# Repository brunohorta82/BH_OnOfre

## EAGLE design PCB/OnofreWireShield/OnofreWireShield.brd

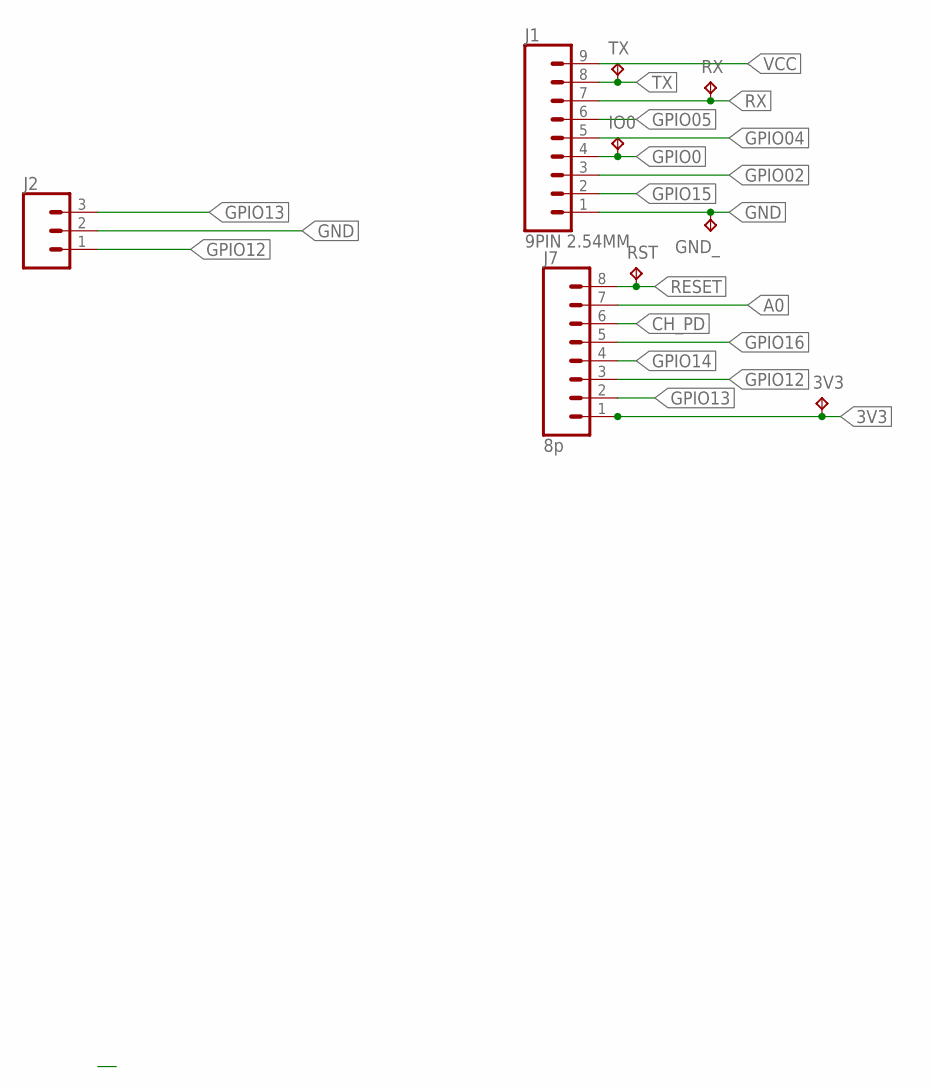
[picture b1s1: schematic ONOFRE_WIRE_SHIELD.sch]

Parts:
3V3: TPB1,27; B1,27
GND_: TPB1,27; B1,27
IO0: TPB1,27; B1,27
J1: 9PIN 2.54MM; 1X09
J2: CONN_03; 1X03
J7: 8p; 1X08
RST: TPB1,27; B1,27
RX: TPB1,27; B1,27
TX: TPB1,27; B1,27

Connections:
3V3: 3V3.TP, J7.1
A0: J7.7
CH_PD: J7.6
GND: GND_.TP, J1.1, J2.2
GPIO0: IO0.TP, J1.4
GPIO02: J1.3
GPIO04: J1.5
GPIO05: J1.6
GPIO12: J2.1, J7.3
GPIO13: J2.3, J7.2
GPIO14: J7.4
GPIO15: J1.2
GPIO16: J7.5
RESET: J7.8, RST.TP
RX: J1.7, RX.TP
TX: J1.8, TX.TP
VCC: J1.9

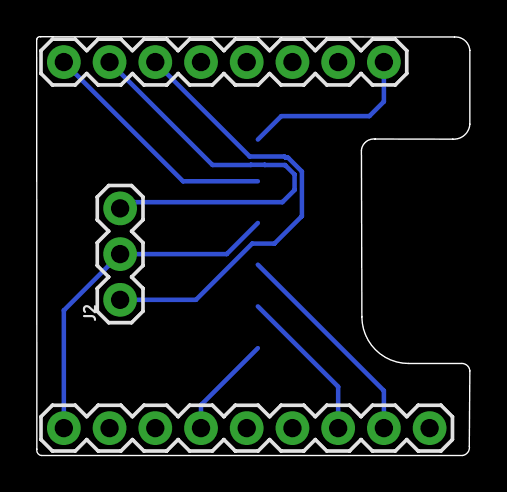
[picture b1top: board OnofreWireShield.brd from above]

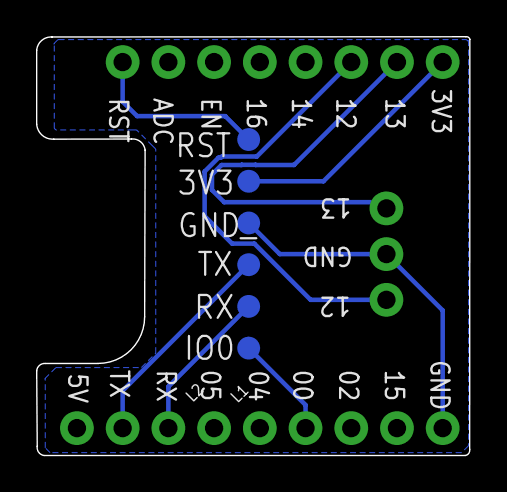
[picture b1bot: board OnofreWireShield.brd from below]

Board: 2 copper layers, 24.1 x 23.3 mm, 9 parts (6 on the bottom side), 8 nets.

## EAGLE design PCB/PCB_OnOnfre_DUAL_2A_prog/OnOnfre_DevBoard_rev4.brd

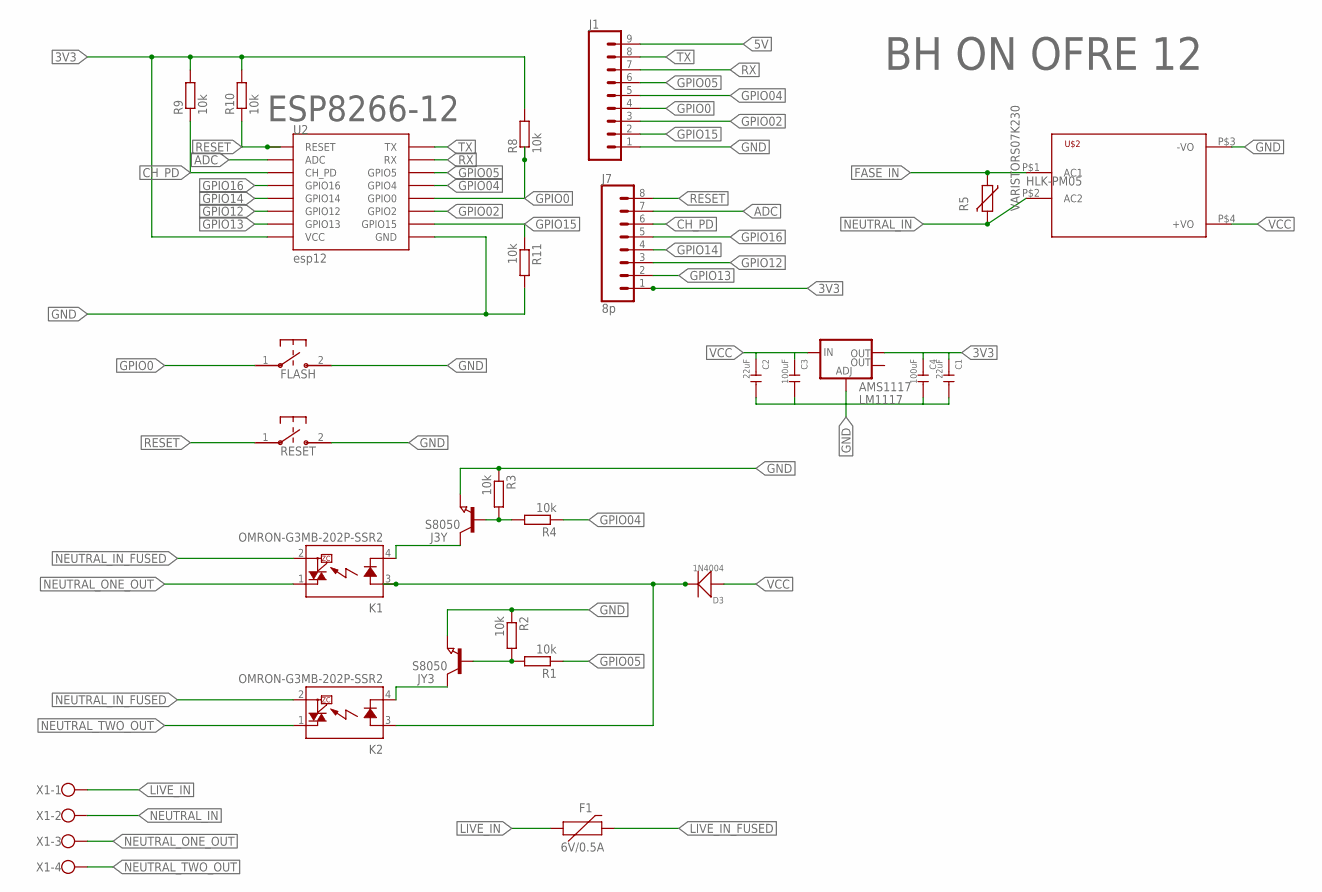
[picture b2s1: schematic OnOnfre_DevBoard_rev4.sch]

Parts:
AMS1117: LM1117; SOT223
C1, C2: 22uF; C1206
C3, C4: 100uF; C1206
D3: 1N4004; DO-214AC
F1: 6V/0.5A; 1206
FLASH: B3U-1000P-2P-SMD; B3U-1000P
J1: CONN_09; 1X09
J3Y: S8050; SOT23
J7: 8p; 1X08
JY3: S8050; SOT23
K1, K2: OMRON-G3MB-202P-SSR2; OMRON-G3MB-202P-SSR
R1, R2, R3, R4, R8, R9, R10, R11: 10k; R0603
R5: VARISTORS07K230; S07K230
RESET: B3U-1000P-2P-SMD; B3U-1000P
U2: esp12; ESP12-SMD
U$2: HKLPM01
X1: W237-4

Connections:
3V3: AMS1117.2 (OUT), C1.1, C4.1, J7.1, R8.2, R9.2, R10.2, U2.VCC
5V: D3.2 (-), J1.9, K1.3 (A), K2.3 (A)
ADC: J7.7, U2.ADC
CH_PD: J7.6, R9.1, U2.CH_PD
FASE_IN: R5.1, U$2.P$1 (AC1)
GND: AMS1117.1 (ADJ), C1.2, C2.2, C3.2, C4.2, FLASH.2, J1.1, J3Y.2 (E), JY3.2 (E), R2.1, R3.1, R11.2, RESET.2, U2.GND, U$2.P$3 (-VO)
GPIO0: FLASH.1, J1.4, R8.1, U2.GPIO0
GPIO02: J1.3, U2.GPIO2
GPIO04: J1.5, R4.1, U2.GPIO4
GPIO05: J1.6, R1.1, U2.GPIO5
GPIO12: J7.3, U2.GPIO12
GPIO13: J7.2, U2.GPIO13
GPIO14: J7.4, U2.GPIO14
GPIO15: J1.2, R11.1, U2.GPIO15
GPIO16: J7.5, U2.GPIO16
LIVE_IN: F1.1, X1.1
LIVE_IN_FUSED: F1.2
unnamed: J3Y.3 (C), K1.4 (K)
unnamed: J3Y.1 (B), R3.2, R4.2
unnamed: JY3.3 (C), K2.4 (K)
unnamed: JY3.1 (B), R1.2, R2.2
NEUTRAL_IN: R5.2, U$2.P$2 (AC2), X1.2
NEUTRAL_IN_FUSED: K1.2 (DS2), K2.2 (DS2)
NEUTRAL_ONE_OUT: K1.1 (DS1), X1.3
NEUTRAL_TWO_OUT: K2.1 (DS1), X1.4
RESET: J7.8, R10.1, RESET.1, U2.RESET
RX: J1.7, U2.RXD0 (RX)
TX: J1.8, U2.TXD0 (TX)
VCC: AMS1117.3 (IN), C2.1, C3.1, D3.1 (+), U$2.P$4 (+VO)

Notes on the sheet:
HLK-PM05
BH ON OFRE 12
ESP8266-12

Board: 2 copper layers, 27 parts (5 on the bottom side), 28 nets, no tracks yet.

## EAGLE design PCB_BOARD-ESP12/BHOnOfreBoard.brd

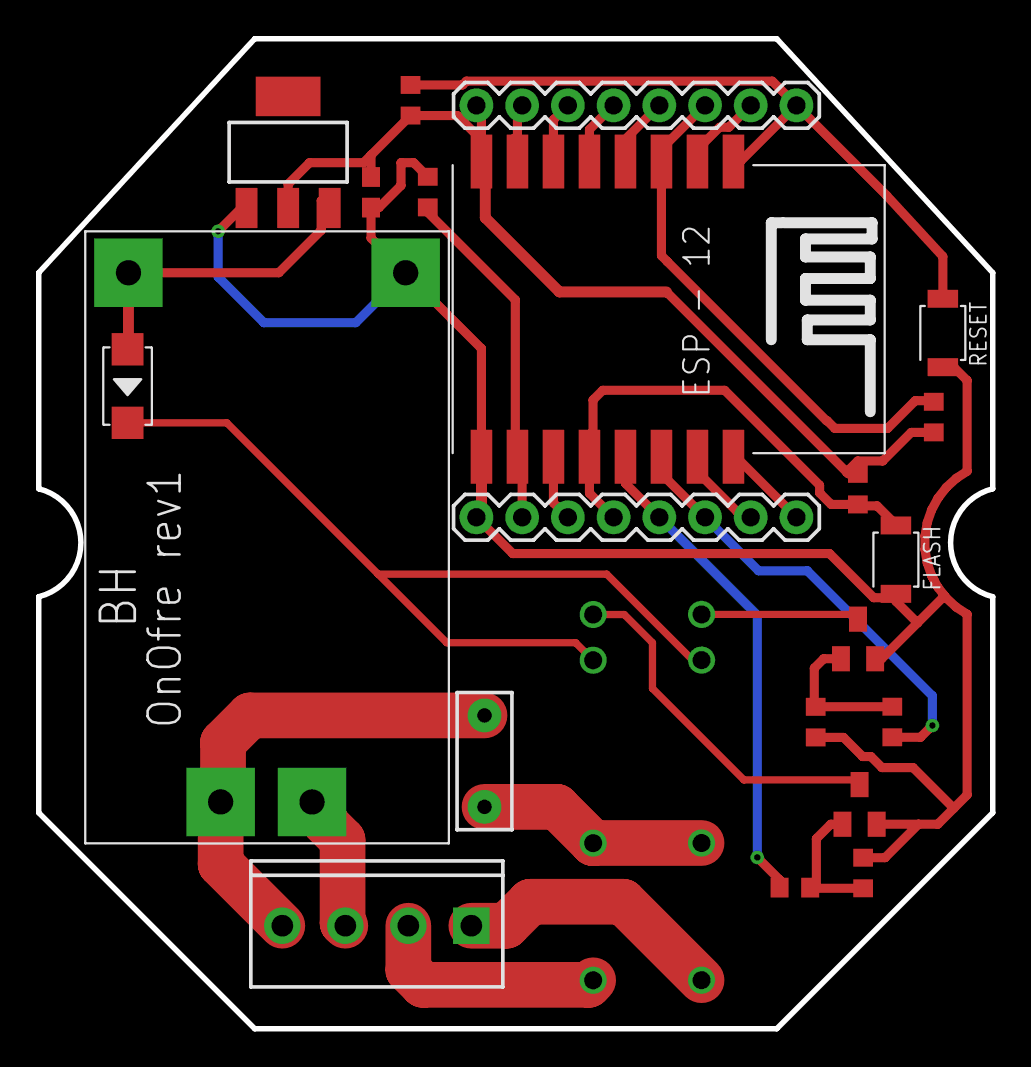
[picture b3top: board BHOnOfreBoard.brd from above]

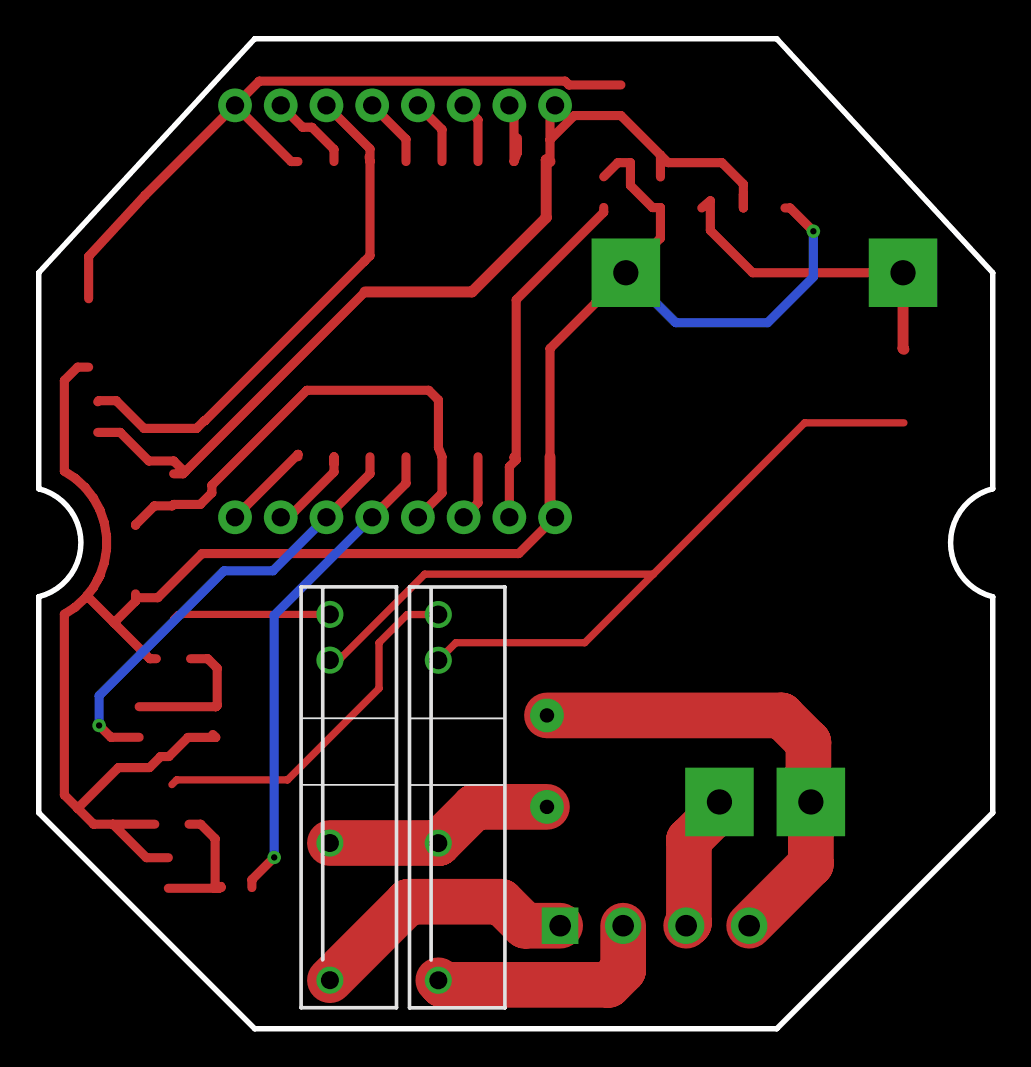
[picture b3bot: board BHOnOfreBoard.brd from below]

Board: 2 copper layers, 53.0 x 55.0 mm, 23 parts (2 on the bottom side), 27 nets.

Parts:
C4: 100nF; 0603
D3: 1N4004; DO-214AC
F1: FUSE 2A; PTH
FLASH: B3U-1000P-2P-SMD; SW2-2.6-3.0X2.5X1.2+0.4MM
J1: 4p; SCREWTERMINAL-3.5MM-4
J6, J7: 8p; 1X08
K1, K2: OMRON-G3MB-202P-SSR2; OMRON-G3MB-202P-SSR
Q1, Q2: S8050; SOT23
R1, R2, R3, R4, R8, R9, R10, R11: 10k; R0603
RESET: B3U-1000P-2P-SMD; SW2-2.6-3.0X2.5X1.2+0.4MM
U1: LM1117; SOT223
U2: esp12; ESP12-SMD
U$2: HLK-PM03

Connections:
3V3: C4.1, J7.1, R8.2, R9.2, R10.2, U1.2, U2.VCC
ADC: J7.7, U2.ADC
CH_PD: J7.6, R9.1, U2.CH_PD
FASE: J1.3, U$2.AC2
GND: C4.2, FLASH.2, J6.1, Q1.2, Q2.2, R2.1, R3.1, R11.2, RESET.2, U1.1, U2.GND, U$2.-VO
GPIO0: FLASH.1, J6.4, R8.1, U2.GPIO0
GPIO02: J6.3, U2.GPIO2
GPIO04: J6.6, R1.1, U2.GPIO4
GPIO05: J6.5, R4.1, U2.GPIO5
GPIO12: J7.3, U2.GPIO12
GPIO13: J7.2, U2.GPIO13
GPIO14: J7.4, U2.GPIO14
GPIO15: J6.2, R11.1, U2.GPIO15
GPIO16: J7.5, U2.GPIO16
unnamed: K1.4, Q1.3
unnamed: D3.2, K1.3, K2.3
unnamed: Q1.1, R3.2, R4.2
unnamed: K2.4, Q2.3
unnamed: Q2.1, R1.2, R2.2
NEUTRAL_IN: F1.P$1, J1.4, U$2.AC1
NEUTRAL_IN_FUSED: F1.P$2, K1.2, K2.2
NEUTRAL_ONE_OUT: J1.2, K1.1
NEUTRAL_TWO_OUT: J1.1, K2.1
RESET: J7.8, R10.1, RESET.1, U2.RESET
RX: J6.7, U2.RXD0
TX: J6.8, U2.TXD0
VCC: D3.1, U1.3, U$2.+VO

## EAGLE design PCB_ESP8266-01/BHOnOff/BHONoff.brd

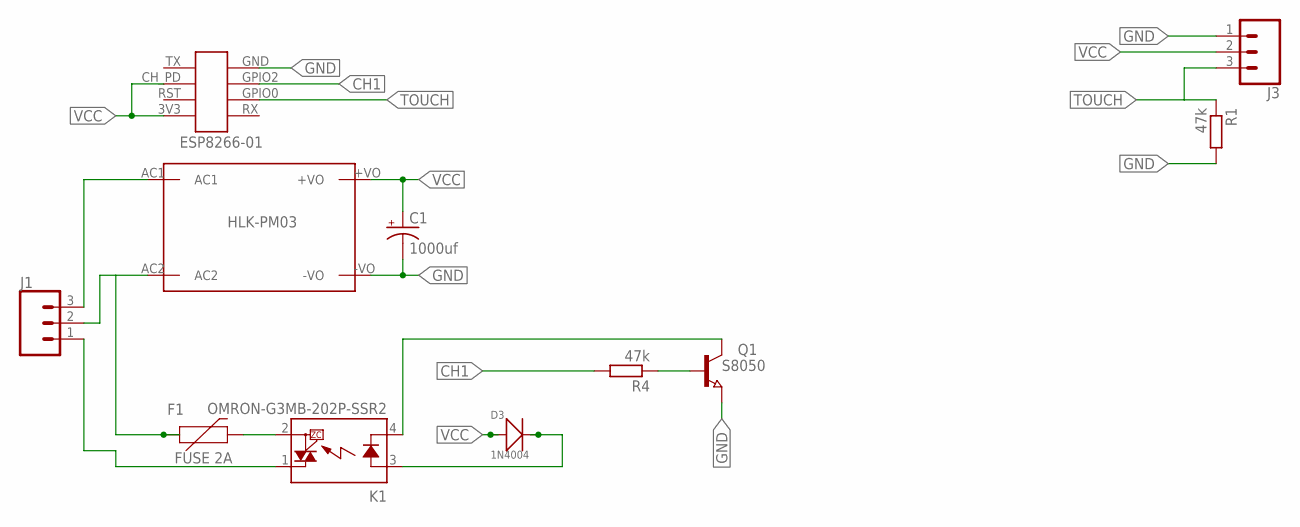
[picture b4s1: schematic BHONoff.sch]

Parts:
C1: 1000uf; 140CLH-1010
D3: 1N4004; DO-214AC
F1: FUSE 2A; PTH
J1: CONN_03-SCREW-5MM; SCREWTERMINAL-5MM-3
J3: CONN_03; 1X03
K1: OMRON-G3MB-202P-SSR2; OMRON-G3MB-202P-SSR
Q1: S8050; SOT23
R1, R4: 47k; R0603
U$2: HLK-PM03
U$3: ESP8266-01

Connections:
CH1: R4.2, U$3.GPIO2
GND: C1.-, J3.1, Q1.2 (E), R1.2, U$2.-VO, U$3.GND
unnamed: K1.4 (K), Q1.3 (C)
unnamed: J1.1, K1.1 (DS1)
unnamed: F1.P$1 (1), J1.2, U$2.AC2
unnamed: J1.3, U$2.AC1
unnamed: F1.P$2 (2), K1.2 (DS2)
unnamed: D3.2 (-), K1.3 (A)
unnamed: Q1.1 (B), R4.1
TOUCH: J3.3, R1.1, U$3.GPIO0
VCC: C1.+, D3.1 (+), J3.2, U$2.+VO, U$3.3V3, U$3.CH_PD

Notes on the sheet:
HLK-PM03
ESP8266-01

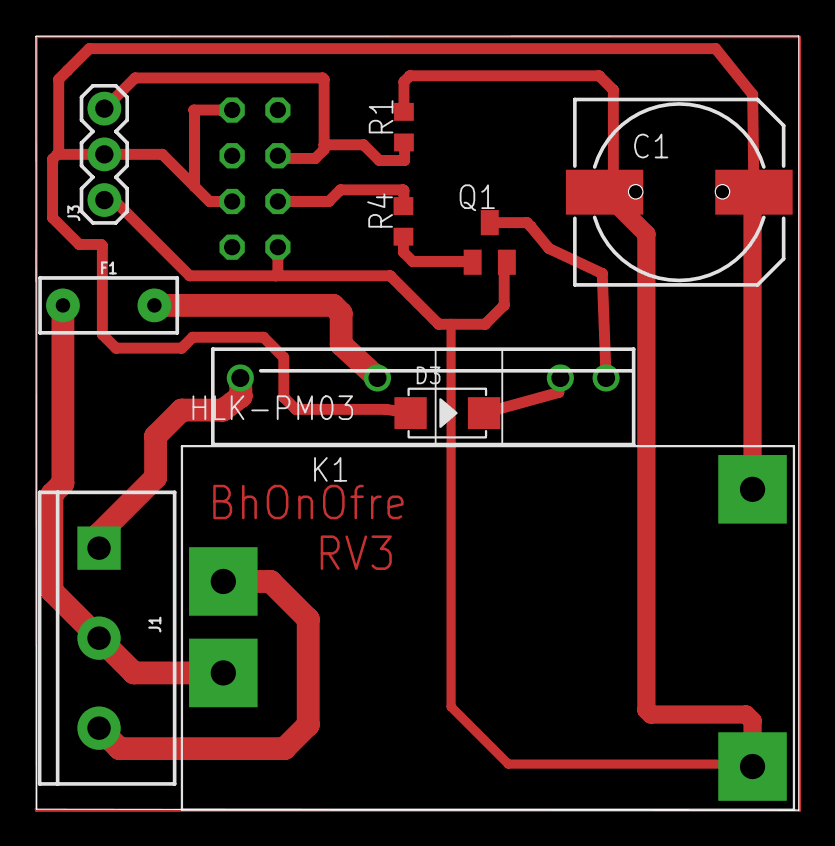
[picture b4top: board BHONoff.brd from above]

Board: 2 copper layers, 42.4 x 43.0 mm, 11 parts (1 on the bottom side), 11 nets.

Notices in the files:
parts and their libraries:
SparkFun-Connectors: Licensing: Creative Commons ShareAlike 4.0 International - https://creativecommons.org/licenses/by-sa/4.0
